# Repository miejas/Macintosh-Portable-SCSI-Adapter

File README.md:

# Macintosh Portable SCSI Adapter
An adapter from the 34-pin SCSI in the Portable to a standard 50-pin header.

Nothing fancy. Just rewires the pins in a convenient fashion, without the need for cobbling cables together. Additionally, there's an option to provide 5V to the TERMPWR pin. This could be achieved with a power diode for "high" current applications (like a SCSI to SD adapter) or a 220/330Ω resistor for current sensing only applications (as described in one of Woz's brain storm documents - can't seem to find it back).

The board has been succesfully produced by JLCPCB and Aisler, so I suppose any manufacturer of choice will do. It probably fits an entire host of different IDC connectors, but they've been succesfully fitted with Samtec's TST-125-01-G-D and TST-117-01-G-D. The 5V-GND-GND-12V "connector" could just be a floppy or hard drive wire bundle, recovered from an old ATX power supply.

The project is in KiCad format and is free for anyone to use, either personally or commercially. Since I have absolutely no experience in schematic and PCB design, there will probably be some errors and "donts". If you happen to find them, please let me know so I can adapt the design accordingly. Needless to say, but use of this project is at your own risk.

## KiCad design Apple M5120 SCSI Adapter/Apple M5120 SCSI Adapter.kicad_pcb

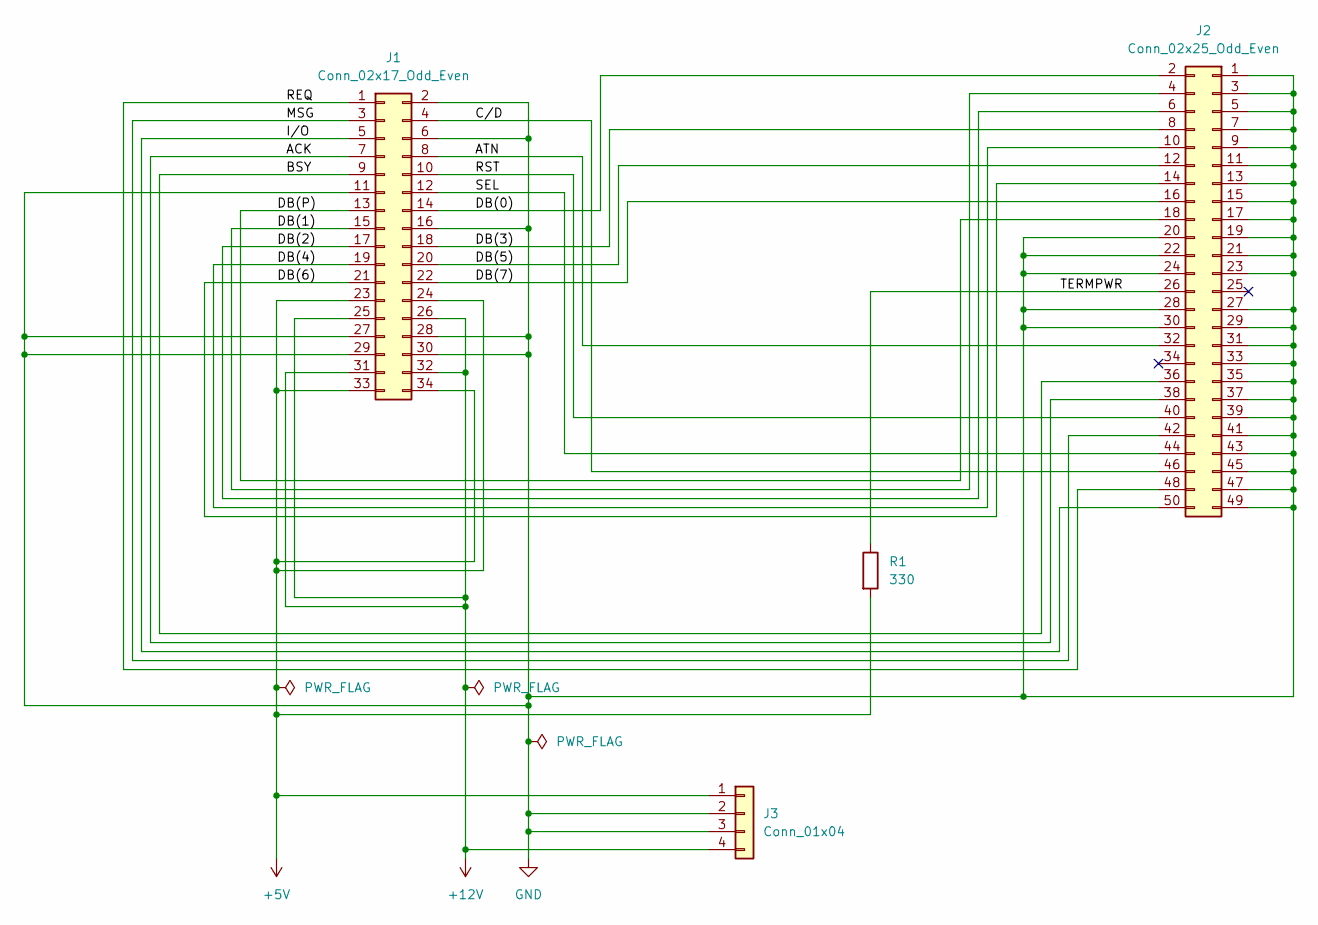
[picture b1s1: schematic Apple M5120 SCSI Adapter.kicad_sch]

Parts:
J1: Conn_02x17_Odd_Even; IDC-Header_2x17_P2.54mm_Vertical
J2: Conn_02x25_Odd_Even; IDC-Header_2x25_P2.54mm_Vertical
J3: Conn_01x04; SolderWire-0.75sqmm_1x04_P7mm_D1.25mm_OD3.5mm
R1: 330; R_Axial_DIN0207_L6.3mm_D2.5mm_P15.24mm_Horizontal

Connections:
+5V: J1.23, J1.24, J1.33, J1.34, J3.1, R1.2
+12V: J1.25, J1.26, J1.31, J1.32, J3.4
/ACK: J1.7, J2.38
/ATN: J1.8, J2.32
/BSY: J1.9, J2.36
/C/D: J1.4, J2.46
/DB(0): J1.14, J2.2
/DB(1): J1.15, J2.4
/DB(2): J1.17, J2.6
/DB(3): J1.18, J2.8
/DB(4): J1.19, J2.10
/DB(5): J1.20, J2.12
/DB(6): J1.21, J2.14
/DB(7): J1.22, J2.16
/DB(P): J1.13, J2.18
/I/O: J1.5, J2.50
/MSG: J1.3, J2.42
/REQ: J1.1, J2.48
/RST: J1.10, J2.40
/SEL: J1.12, J2.44
/TERMPWR: J2.26, R1.1
GND: J1.2, J1.6, J1.11, J1.16, J1.27, J1.28, J1.29, J1.30, J2.1, J2.3, J2.5, J2.7, J2.9, J2.11, J2.13, J2.15, J2.17, J2.19, J2.20, J2.21, J2.22, J2.23, J2.24, J2.27, J2.28, J2.29, J2.30, J2.31, J2.33, J2.35, J2.37, J2.39, J2.41, J2.43, J2.45, J2.47, J2.49, J3.2, J3.3

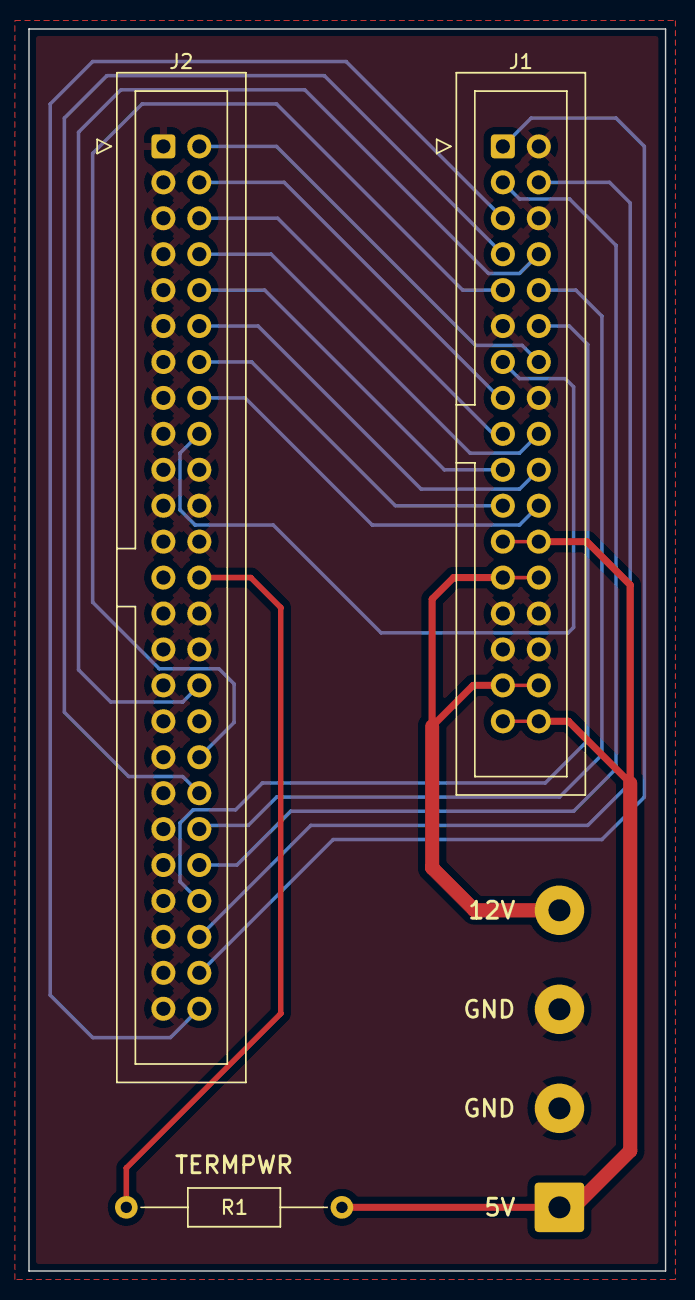
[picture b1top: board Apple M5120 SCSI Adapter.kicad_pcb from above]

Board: 2 copper layers, 45.0 x 87.8 mm, 4 parts (0 on the bottom side), 22 nets.

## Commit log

2022-11-06 Update LICENSE
2022-11-06 Create LICENSE
